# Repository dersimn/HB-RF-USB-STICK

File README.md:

Smaller version of [HB-RF-USB](https://github.com/alexreinert/PCB). Electrically identical.  
Can be used to emulate a Homematic CCU with [RaspberryMatic](https://github.com/jens-maus/RaspberryMatic) in a virtual machine on x86 architecture.

The HM-MOD-RPI-PCB kit comes with pre-soldered pins on the HM-MOD-UART-AW-SH-2. You have to desolder them first:

## Required Parts

Shopping list with all used parts on [Reichelt](https://www.reichelt.de/my/1737625). You have to buy also one HM-MOD-RPI-PCB from ELV.

List:

- R (SMD 1206)
    - 1x 1 MΩ: [Reichelt](https://www.reichelt.de/smd-widerstand-1206-1-0-mohm-250-mw-1-rnd-1206-1-1m-p183429.html?&trstct=pol_0&nbc=1)
    - 1x 10 kΩ: [Reichelt](https://www.reichelt.de/smd-widerstand-1206-10-kohm-250-mw-1-rnd-1206-1-10k-p183394.html?&trstct=pol_0&nbc=1)
    - 3x 1 kΩ: [Reichelt](https://www.reichelt.de/smd-widerstand-1206-1-0-kohm-250-mw-1-rnd-1206-1-1-0k-p183379.html?&trstct=pol_2&nbc=1)
- C (SMD 1206)
    - 1x 100 µF: [Reichelt](https://www.reichelt.de/smd-vielschichtkondensator-g1206-100-f-6-3v-x5r-g1206-100-6-p89744.html?&trstct=pol_0&nbc=1)
    - 1x 4.7 µF: [Reichelt](https://www.reichelt.de/smd-kerko-1206-4-7-f-50-v-10-mlcc-rnd-1501206b475k-p254230.html?&trstct=pol_0&nbc=1)
    - 3x 100 nF: [Reichelt](https://www.reichelt.de/vielschicht-kerko-100nf-50v-125-c-kem-x7r1206b100n-p207152.html?&nbc=1)
    - 1x 10 nF: [Reichelt](https://www.reichelt.de/vielschicht-kerko-10nf-50v-125-c-kem-x7r1206b10n-p207144.html?&trstct=pol_3&nbc=1)
    - 1x 4.7 nF: [Reichelt](https://www.reichelt.de/vielschicht-kerko-4-7nf-50v-125-c-kem-x7r1206-4-7n-p207141.html?&trstct=pol_5&nbc=1)
- L (SMD 1206)
    - ≥33 nH; ≤1 Ω (DC): [Reichelt](https://www.reichelt.de/smd-induktivitaet-1206-keramik-220n-l-1206as-220n-p72972.html?&trstct=pol_11&nbc=1)
- IC
    - 1x FT232RL: [Reichelt](https://www.reichelt.de/rs232-interface-bruecke-usb-zu-uart-ssop-28-ft-232-rl-p64399.html?&nbc=1)
    - 1x HM-MOD-UART-AW-SH-2 (included in HM-MOD-RPI-PCB): [ELV](https://de.elv.com/elv-homematic-komplettbausatz-funkmodul-fuer-raspberry-pi-hm-mod-rpi-pcb-fuer-smart-home-hausautomation-142141)
- Misc
    - 1x IRLML6402: [Reichelt](https://www.reichelt.de/mosfet-p-ch-20v-3-7a-1-3w-sot-23-irlml-6402-p108743.html?&nbc=1)
    - 1x A-USB A-LP-SMT-C: [Reichelt](https://www.reichelt.de/usb-einbaustecker-serie-a-gerade-180-vers-usb-agf-p52008.html?&nbc=1), [Conrad](https://www.conrad.de/de/p/usb-stecker-ultra-flach-stecker-einbau-a-usb-a-lp-smt-c-usb-a-smt-assmann-wsw-inhalt-1-st-741461.html)

## Order PCB

Use the provided Gerber files under Releases in the GitHub repository or generate your own CAM using Autodesk EAGLE.

I ordered the PCBs from [JLCPCB](https://jlcpcb.com). If you use their service you have to specify dimensions `33 x 16 mm` in the order mask and also add the Remark

> 2x Slotted Holes

## Flash FTDI

Get FT_Prog from [here](https://www.ftdichip.com/Support/Utilities.htm#FT_PROG). Use [`FT232R_Template.xml`](contrib/FT232R_Template.xml) for configuration:

## Credits

- [@alexreinert/HB-RF-USB](https://github.com/alexreinert/PCB): Original idea.
- [@stan23/HB-MOD-UART-USB](https://github.com/stan23/myPCBs/tree/master/HB-MOD-UART-USB): Same goal as this project, but probably harder to solder due to 0603 SMD parts.

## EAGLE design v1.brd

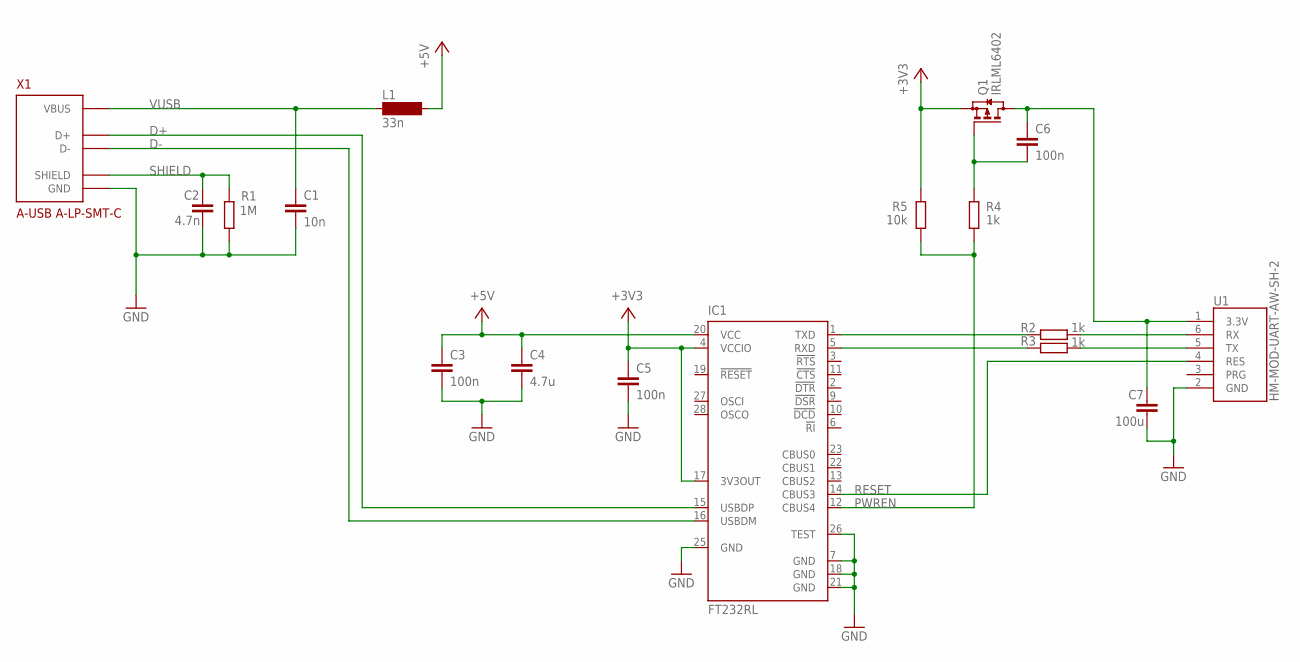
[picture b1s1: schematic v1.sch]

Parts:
C1: 10n; C1206
C2: 4.7n; C1206
C3, C5, C6: 100n; C1206
C4: 4.7u; C1206
C7: 100u; C1206
IC1: FT232RL; SSOP28
L1: 33n; SM-1206
Q1: IRLML6402; SOT23
R1: 1M; R1206
R2, R3, R4: 1k; R1206
R5: 10k; R1206
U1: HM-MOD-UART-AW-SH-2; HM-MOD-UART-AW-SH-2_SMD
X1: A-USB A-LP-SMT-C; A-USB_A-LP-SMT-C

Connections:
+3V3: C5.1, IC1.4 (VCCIO), IC1.17 (3V3OUT), Q1.2 (S), R5.2
+5V: C3.1, C4.1, IC1.20 (VCC), L1.2
D+: IC1.15 (USBDP), X1.3 (D+)
D-: IC1.16 (USBDM), X1.2 (D-)
GND: C1.2, C2.2, C3.2, C4.2, C5.2, C7.2, IC1.7 (GND), IC1.18 (GND), IC1.21 (GND), IC1.25 (GND), IC1.26 (TEST), R1.2, U1.2 (GND), X1.4 (GND)
unnamed: C6.1, C7.1, Q1.3 (D), U1.1 (3.3V)
unnamed: R2.2, U1.6 (RX)
unnamed: R3.2, U1.5 (TX)
unnamed: IC1.1 (TXD), R2.1
unnamed: IC1.5 (RXD), R3.1
unnamed: C6.2, Q1.1 (G), R4.2
PWREN: IC1.12 (CBUS4), R4.1, R5.1
RESET: IC1.14 (CBUS3), U1.4 (RES)
SHIELD: C2.1, R1.1, X1.S1 (SHIELD), X1.S2 (SHIELD)
VUSB: C1.1, L1.1, X1.1 (VBUS)

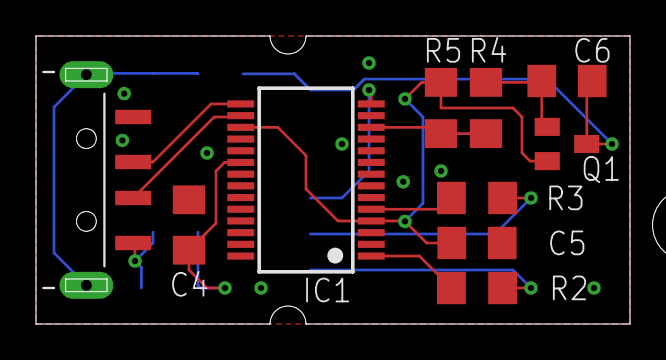
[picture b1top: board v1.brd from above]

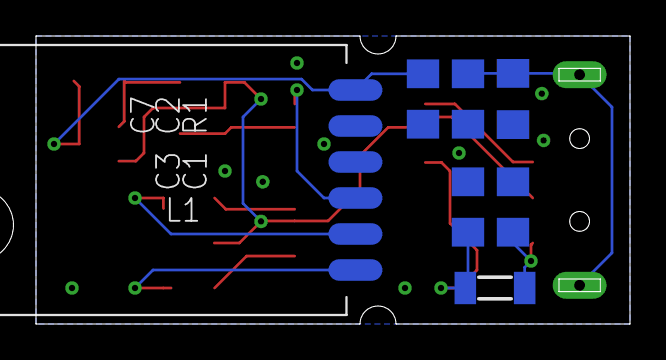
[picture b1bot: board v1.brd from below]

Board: 2 copper layers, 33.0 x 16.0 mm, 17 parts (7 on the bottom side), 15 nets.

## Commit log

2020-07-24 Init
2020-07-25 README
2020-07-25 Default view
2020-07-25 Cover vias with solder restist
2020-09-15 Fix not connected pin TEST
2020-09-15 Docs
2020-09-15 Thumbnail size
2020-09-15 Fix image links
2020-09-17 Add instructions to flash FTDI chip

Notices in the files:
parts and their libraries:
homematic: CC Attribution-ShareAlike 4.0 International (CC BY-SA 4.0)
